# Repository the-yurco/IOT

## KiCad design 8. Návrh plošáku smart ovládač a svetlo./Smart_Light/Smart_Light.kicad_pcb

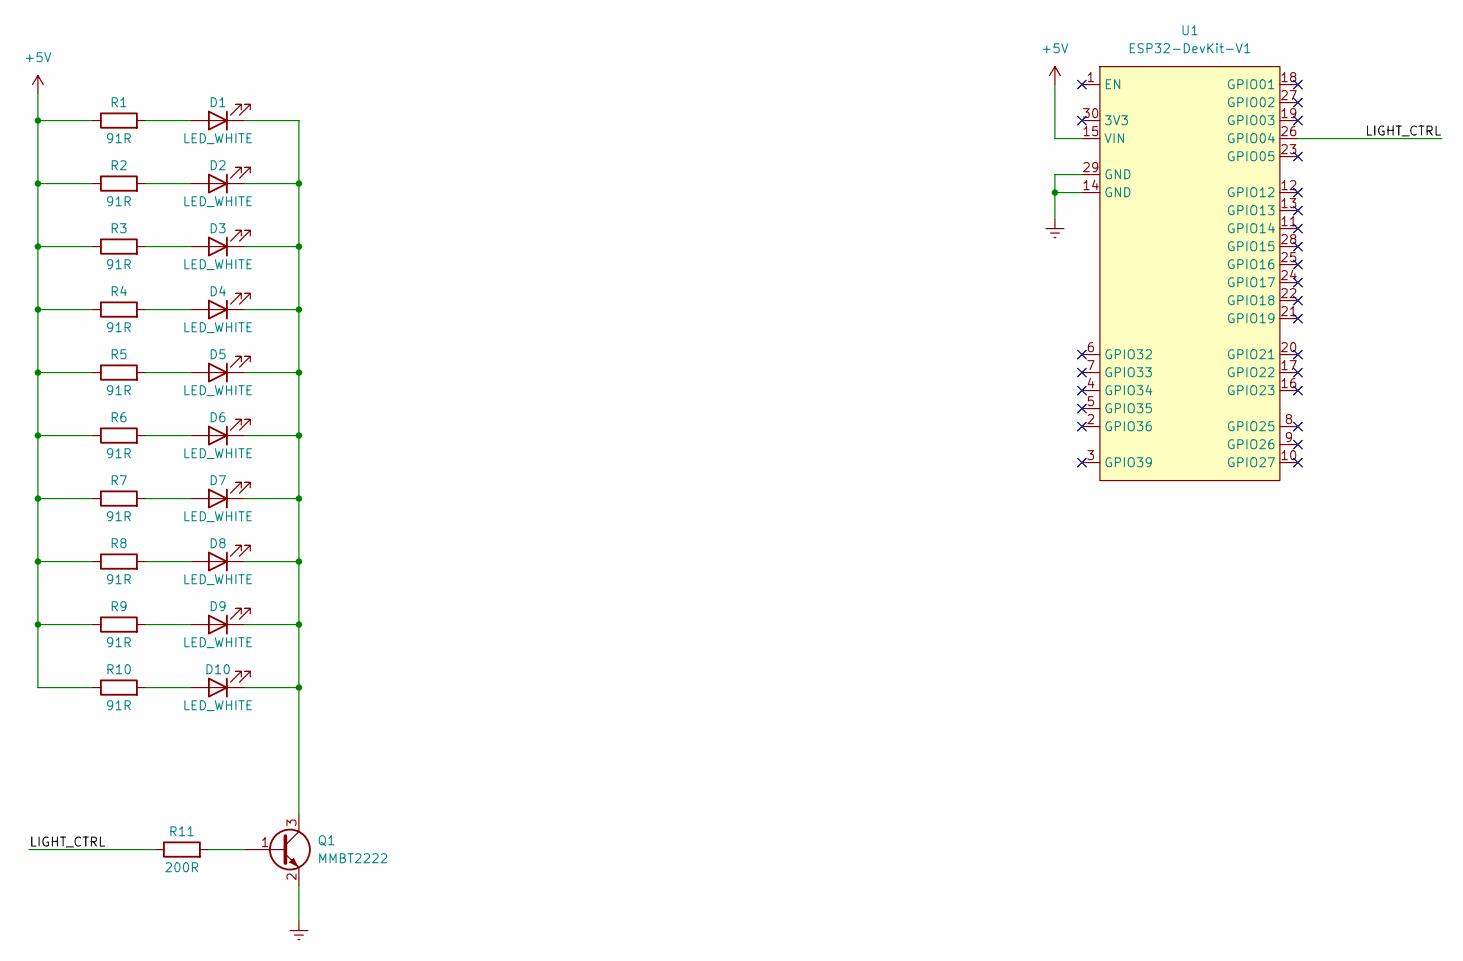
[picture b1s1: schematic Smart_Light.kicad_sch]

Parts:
D1, D2, D3, D4, D5, D6, D7, D8, D9, D10: LED_WHITE; PLCC2
Q1: MMBT2222; SOT-323_SC-70
R1, R2, R3, R4, R5, R6, R7, R8, R9, R10: 91R; R_0805_2012Metric
R11: 200R; R_0805_2012Metric
U1: ESP32-DevKit-V1

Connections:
+5V: R1.1, R2.1, R3.1, R4.1, R5.1, R6.1, R7.1, R8.1, R9.1, R10.1, U1.15 (VIN)
/LIGHT_CTRL: R11.1, U1.26 (GPIO04)
Earth: Q1.2 (E), U1.14 (GND), U1.29 (GND)
unnamed: D1.2 (A), R1.2
unnamed: D1.1 (K), D2.1 (K), D3.1 (K), D4.1 (K), D5.1 (K), D6.1 (K), D7.1 (K), D8.1 (K), D9.1 (K), D10.1 (K), Q1.3 (C)
unnamed: D2.2 (A), R2.2
unnamed: D3.2 (A), R3.2
unnamed: D4.2 (A), R4.2
unnamed: D5.2 (A), R5.2
unnamed: D6.2 (A), R6.2
unnamed: D7.2 (A), R7.2
unnamed: D8.2 (A), R8.2
unnamed: D9.2 (A), R9.2
unnamed: D10.2 (A), R10.2
unnamed: Q1.1 (B), R11.2

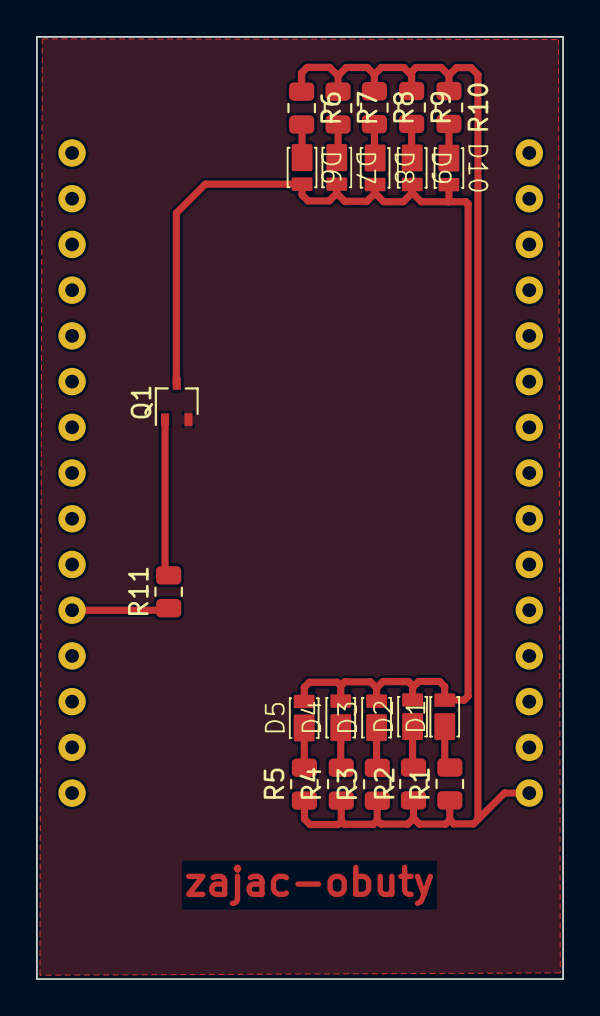
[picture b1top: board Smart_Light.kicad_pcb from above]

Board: 2 copper layers, 29.2 x 52.3 mm, 23 parts (1 on the bottom side), 15 nets.

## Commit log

2024-01-10 feat: update
